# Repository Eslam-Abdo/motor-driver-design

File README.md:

# Motor Driver Design
This repository contains the latest version of my motor driver design project. My role in the project included reverse engineering a Cytron 10-A motor driver, redesigning the driver circuit using Eagle PCB tool, and designing multiple versions to improve the design.

## Latest Version
Below is a picture of the latest version of the motor driver circuit board:

|  |  |  |
| ------- | ------- | ------- |
|  |  |  |
|  |  |  |
|  |  | | |

## Files
The repository contains the following files:
- Schematics and PCB layout files for different versions of the motor driver circuit
- Pictures of the fabricated PCBs for each version

## Contact
If you are interested in my services for your next PCB design and fabrication project, please feel free to contact me.

Email: **eng-islam-abdo1722@alexu.edu.eg**

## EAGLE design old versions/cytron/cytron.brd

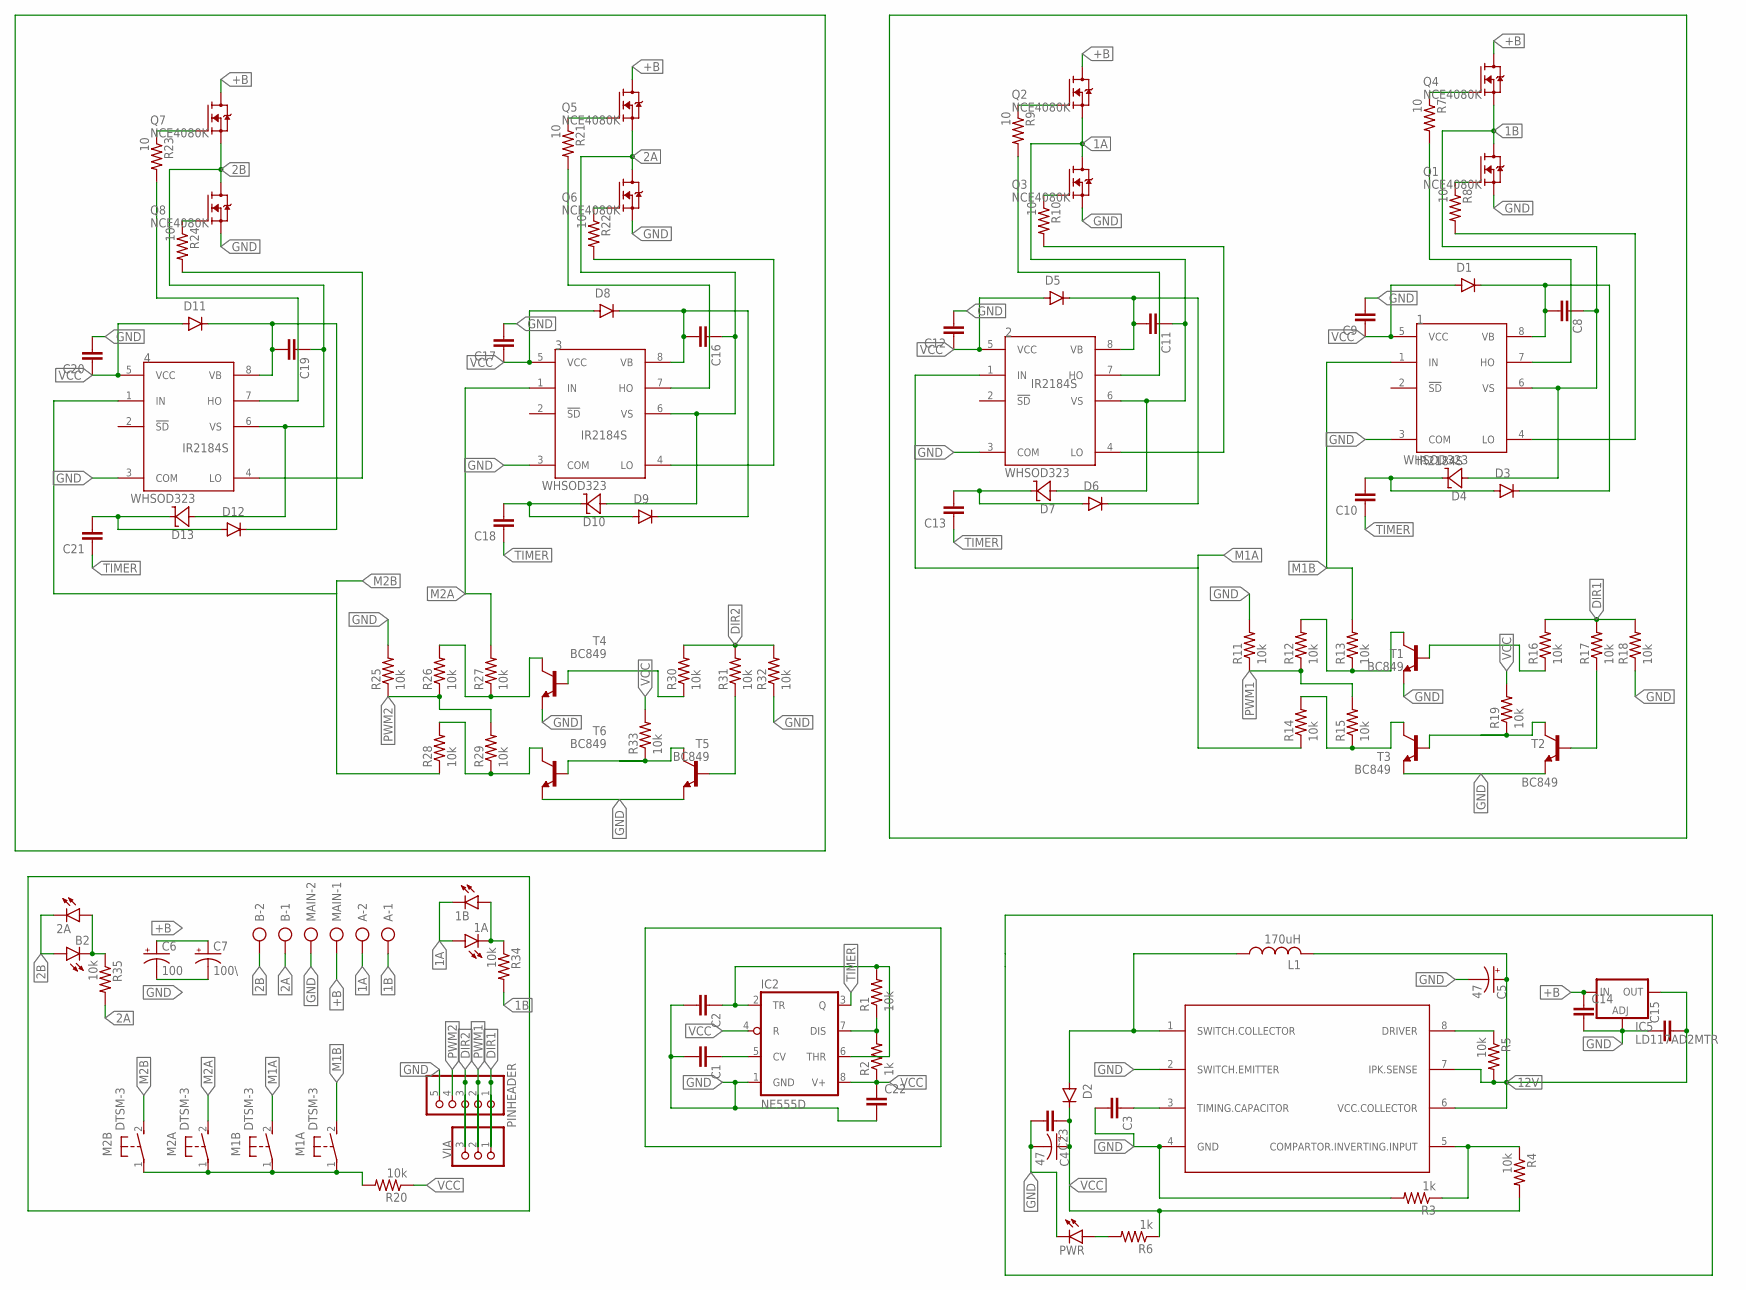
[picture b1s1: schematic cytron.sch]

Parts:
1, 2, 3, 4: IR2184S; SO08
1A, 1B, 2A: LEDCHIPLED_1206; CHIPLED_1206
A: AK300/22; XTALRR488W60L1090T465H350B
B: AK300/22; XTALRR488W60L1090T465H350B
B2: LEDCHIPLED_1206; CHIPLED_1206
C1, C2, C3, C8, C9, C10, C11, C12, C13, C14, C15, C16, C17, C18, C19, C20, C21, C22, C23: C-EUC0805K; C0805K
C4, C5: 47; 140CLH-1014
C6: 100; SANYO-OSCON_SMD_F12
C7: 100\; SANYO-OSCON_SMD_F12
D1, D2, D3, D5, D6, D8, D9, D11, D12: DIODE-SMB; SMB
D4, D7, D10, D13: WHSOD323; SOD323-W
IC2: NE555D; SO08
IC5: LD117AD2MTR; D2PACK
L1: 170uH; POWER-CHOKE_WE-TPC
M1A, M1B, M2A, M2B: DTSM-3
MAIN: AK300/22; XTALRR488W60L1090T465H350B
PINHEADER: PINHD-1X5; 1X05
PWR: LEDCHIPLED_1206; CHIPLED_1206
Q1, Q2, Q3, Q4, Q5, Q6, Q7, Q8: NCE4080K; TO252
R1, R4, R5, R11, R12, R13, R14, R15, R16, R17, R18, R19, R20, R25, R26, R27, R28, R29, R30, R31, R32, R33, R34, R35: 10k; R1206
R2, R3, R6: 1k; R1206
R7, R8, R9, R10, R21, R22, R23, R24: 10; R1206
T1, T2, T3, T4, T5, T6: BC849; SOT23
U$1: AB34063; SO8
VIA: PINHD-1X3; 1X03

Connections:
1A: 1A.A, 1B.C, 2.6 (VS), A.2, C11.1, D7.A, Q2.2 (S), Q3.3 (D)
1B: 1.6 (VS), A.1, C8.1, D4.A, Q1.3 (D), Q4.2 (S), R34.2
2A: 3.6 (VS), B.1, C16.1, D10.A, Q5.2 (S), Q6.3 (D), R35.2
2B: 2A.C, 4.6 (VS), B.2, B2.A, C19.1, D13.A, Q7.2 (S), Q8.3 (D)
12V: C5.+, C15.2, IC5.3 (OUT), L1.2, R5.2, U$1.6 (VCC.COLLECTOR), U$1.7 (IPK.SENSE)
+B: C6.+, C7.+, C14.1, IC5.1 (IN), MAIN.1, Q2.3 (D), Q4.3 (D), Q5.3 (D), Q7.3 (D)
DIR1: PINHEADER.1, R16.2, R17.2, R18.2, VIA.1
DIR2: PINHEADER.3, R30.2, R31.2, R32.2, VIA.3
GND: 1.3 (COM), 2.3 (COM), 3.3 (COM), 4.3 (COM), C1.2, C2.2, C3.2, C4.-, C5.-, C6.-, C7.-, C9.2, C12.2, C14.2, C15.1, C17.2, C20.2, C22.2, C23.2, IC2.1 (GND), IC5.2 (ADJ), MAIN.2, PINHEADER.5, PWR.C, Q1.2 (S), Q3.2 (S), Q6.2 (S), Q8.2 (S), R3.2, R11.2, R18.1, R25.2, R32.1, T1.2 (E), T2.2 (E), T3.2 (E), T4.2 (E), T5.2 (E), T6.2 (E), U$1.2 (SWITCH.EMITTER), U$1.4 (GND)
M1A: 2.1 (IN), M1B.2, R14.1
M1B: 1.1 (IN), M1A.2, R13.2
M2A: 3.1 (IN), M2A.2, R27.2
M2B: 4.1 (IN), M2B.2, R28.1
unnamed: PWR.A, R6.2
unnamed: C1.1, IC2.5 (CV)
unnamed: IC2.7 (DIS), R1.1, R2.2
unnamed: C2.1, IC2.2 (TR), IC2.6 (THR), R1.2
unnamed: C3.1, U$1.3 (TIMING.CAPACITOR)
unnamed: Q6.1 (G), R22.1
unnamed: D2.A, L1.1, U$1.1 (SWITCH.COLLECTOR)
unnamed: R5.1, U$1.8 (DRIVER)
unnamed: Q4.1 (G), R7.1
unnamed: Q1.1 (G), R8.1
unnamed: R3.1, R4.1, U$1.5 (COMPARTOR.INVERTING.INPUT)
unnamed: 1.4 (LO), R8.2
unnamed: 1.7 (HO), R7.2
unnamed: C10.2, D3.A, D4.C
unnamed: Q3.1 (G), R10.1
unnamed: Q2.1 (G), R9.1
unnamed: 2.4 (LO), R10.2
unnamed: 2.7 (HO), R9.2
unnamed: R16.1, T1.1 (B)
unnamed: C13.2, D6.A, D7.C
unnamed: M1A.1, M1B.1, M2A.1, M2B.1, R20.2
unnamed: R14.2, R15.1, T3.3 (C)
unnamed: R12.2, R13.1, T1.3 (C)
unnamed: Q5.1 (G), R21.1
unnamed: 3.4 (LO), R22.2
unnamed: R19.1, T2.3 (C), T3.1 (B)
unnamed: R17.1, T2.1 (B)
unnamed: 3.7 (HO), R21.2
unnamed: C18.2, D9.A, D10.C
unnamed: Q8.1 (G), R24.1
unnamed: Q7.1 (G), R23.1
unnamed: 4.4 (LO), R24.2
unnamed: 4.7 (HO), R23.2
unnamed: C21.2, D12.A, D13.C
unnamed: R28.2, R29.1, T6.3 (C)
unnamed: R26.2, R27.1, T4.3 (C)
unnamed: R30.1, T4.1 (B)
unnamed: R33.1, T5.3 (C), T6.1 (B)
unnamed: R31.1, T5.1 (B)
unnamed: 1A.C, 1B.A, R34.1
unnamed: 2A.A, B2.C, R35.1
PWM1: PINHEADER.2, R11.1, R12.1, R15.2, VIA.2
PWM2: PINHEADER.4, R25.1, R26.1, R29.2
TIMER: C10.1, C13.1, C18.1, C21.1, IC2.3 (Q)
VB1: 1.8 (VB), C8.2, D1.C, D3.C
VB2: 2.8 (VB), C11.2, D5.C, D6.C
VB3: 3.8 (VB), C16.2, D8.C, D9.C
VB4: 4.8 (VB), C19.2, D11.C, D12.C
VCC: 1.5 (VCC), 2.5 (VCC), 3.5 (VCC), 4.5 (VCC), C4.+, C9.1, C12.1, C17.1, C20.1, C22.1, C23.1, D1.A, D2.C, D5.A, D8.A, D11.A, IC2.4 (R), IC2.8 (V+), R2.1, R4.2, R6.1, R19.2, R20.1, R33.2

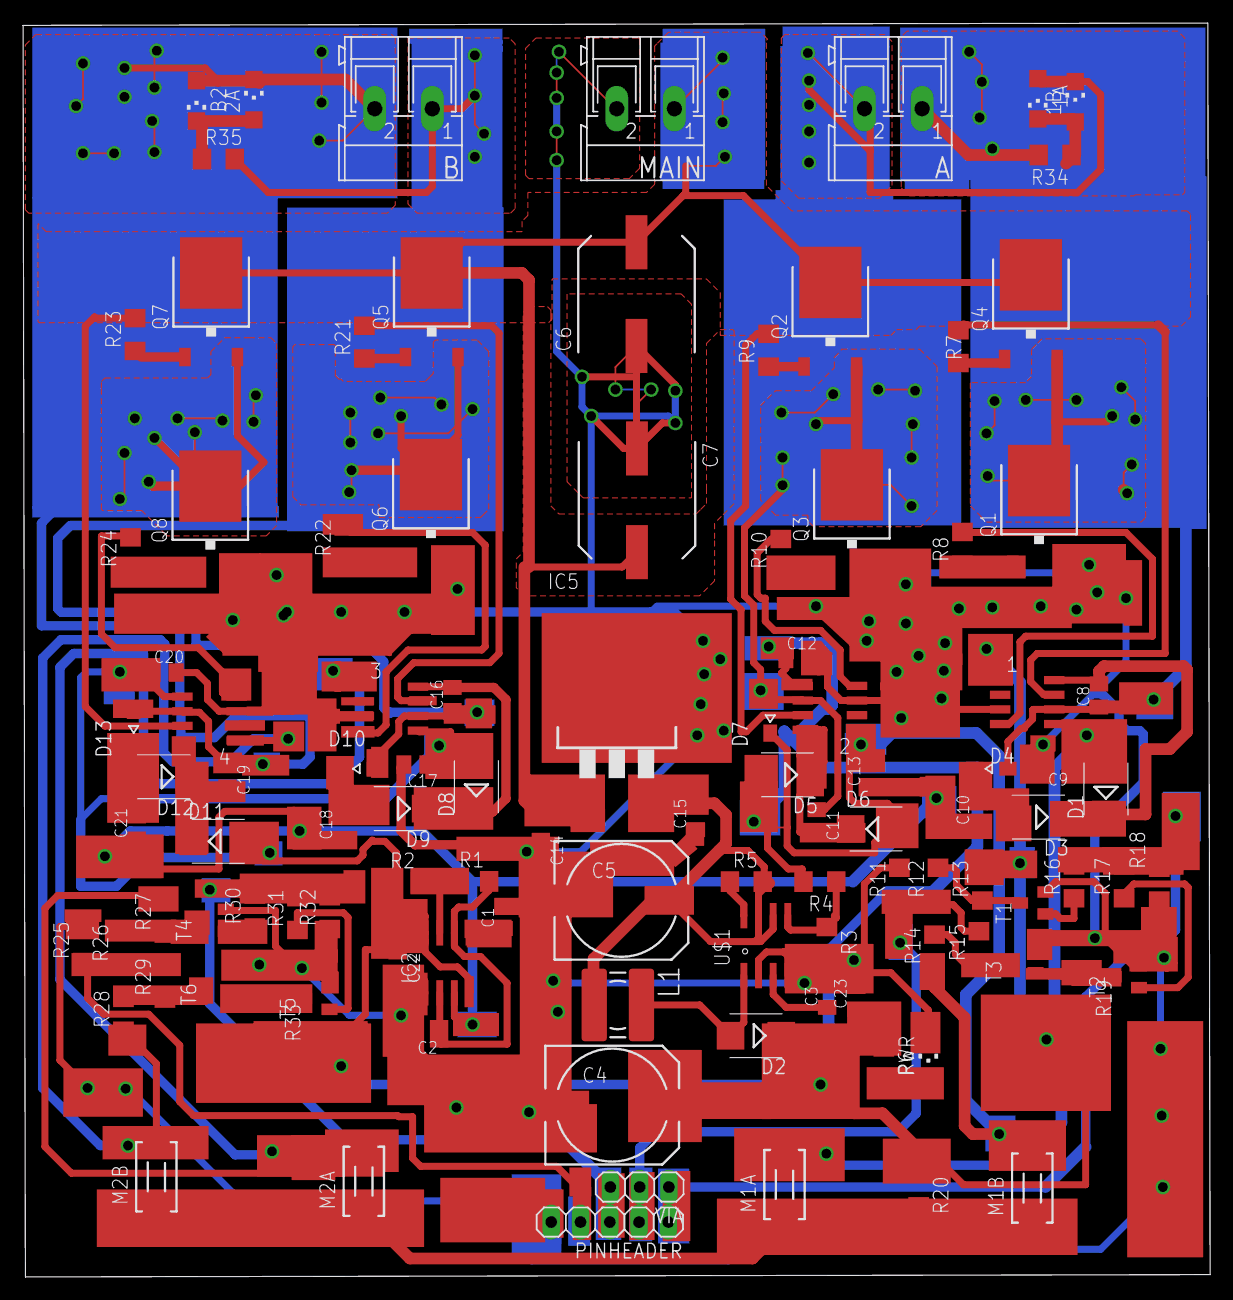
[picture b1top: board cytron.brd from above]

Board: 2 copper layers, 103.0 x 108.8 mm, 107 parts (0 on the bottom side), 62 nets.

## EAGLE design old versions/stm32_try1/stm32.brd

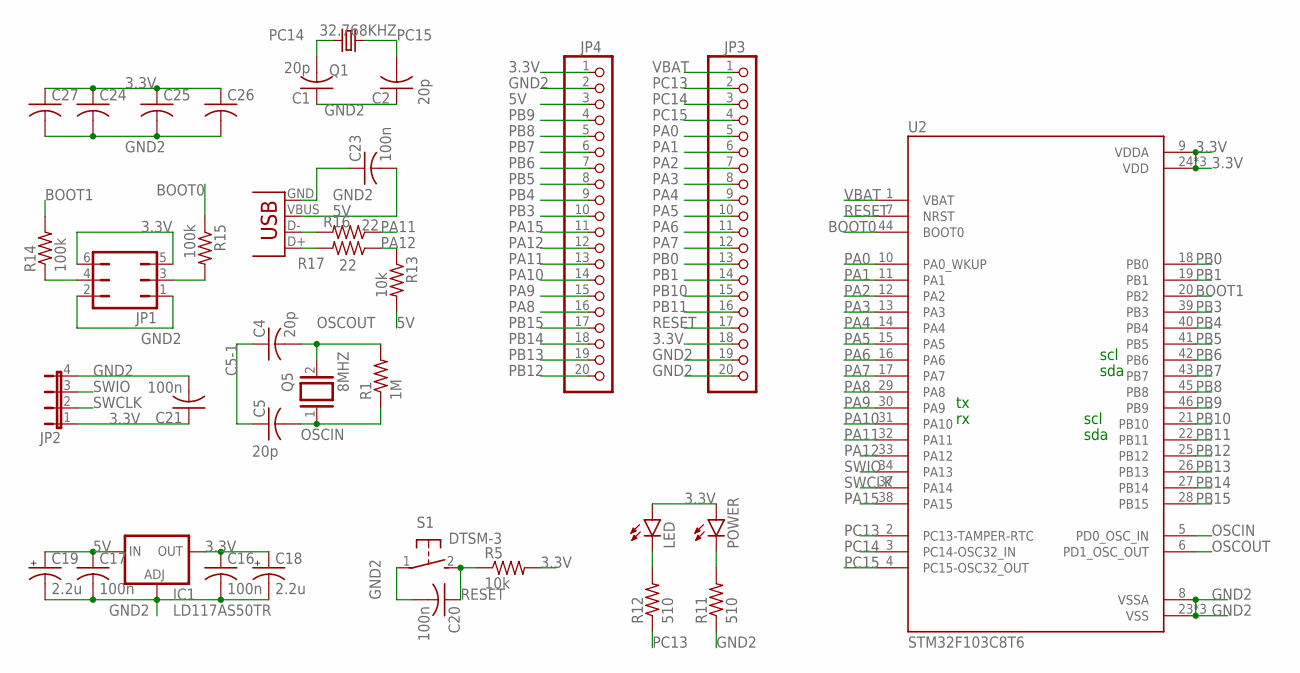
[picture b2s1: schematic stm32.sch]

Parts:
C1, C2, C4, C5: 20p; C1206
C16, C17, C20, C21, C23: 100n; C1206
C18, C19: 2.2u; E2-5
C24, C25, C26, C27: C-USC1206; C1206
IC1: LD117AS50TR; SOT223
JP1: JP3Q
JP2: JP4E; JP4
JP3, JP4: PINHD-1X20; 1X20
LED: LEDCHIPLED_1206; CHIPLED_1206
POWER: LEDCHIPLED_1206; CHIPLED_1206
Q1: 32.768KHZ; TC26H
Q5: 8MHZ; QS
R1: 1M; R1206
R5, R13: 10k; R1206
R11, R12: 510; R1206
R14, R15: 100k; R1206
R16, R17: 22; R1206
S1: DTSM-3
U2: STM32F103C8T6; QFP50P900X900X160-48N
X1: USB-MB-S

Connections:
3.3V: C16.1, C18.+, C21.1, C24.1, C25.1, C26.1, C27.1, IC1.4 (OUT), JP1.5, JP1.6, JP2.1, JP3.18, JP4.1, LED.A, POWER.A, R5.2, U2.9 (VDDA), U2.24 (VDD), U2.36 (VDD), U2.48 (VDD)
5V: C17.1, C19.+, C23.2, IC1.3 (IN), JP4.3, R13.2, X1.VBUS
BOOT0: R15.1, U2.44 (BOOT0)
BOOT1: R14.2, U2.20 (PB2)
C5-1: C4.1, C5.1
GND2: C1.1, C2.1, C16.2, C17.2, C18.-, C19.-, C20.2, C21.2, C23.1, C24.2, C25.2, C26.2, C27.2, IC1.1 (ADJ), JP1.1, JP1.2, JP2.4, JP3.19, JP3.20, JP4.2, R11.1, S1.1, U2.8 (VSSA), U2.23 (VSS), U2.35 (VSS), U2.47 (VSS), X1.GND
unnamed: LED.C, R12.2
unnamed: POWER.C, R11.2
unnamed: JP1.3, R15.2
unnamed: JP1.4, R14.1
unnamed: R16.2, X1.D-
unnamed: R17.2, X1.D+
OSCIN: C5.2, Q5.1, R1.1, U2.5 (PD0_OSC_IN)
OSCOUT: C4.2, Q5.2, R1.2, U2.6 (PD1_OSC_OUT)
PA0: JP3.5, U2.10 (PA0_WKUP)
PA1: JP3.6, U2.11 (PA1)
PA2: JP3.7, U2.12 (PA2)
PA3: JP3.8, U2.13 (PA3)
PA4: JP3.9, U2.14 (PA4)
PA5: JP3.10, U2.15 (PA5)
PA6: JP3.11, U2.16 (PA6)
PA7: JP3.12, U2.17 (PA7)
PA8: JP4.16, U2.29 (PA8)
PA9: JP4.15, U2.30 (PA9)
PA10: JP4.14, U2.31 (PA10)
PA11: JP4.13, R16.1, U2.32 (PA11)
PA12: JP4.12, R13.1, R17.1, U2.33 (PA12)
PA15: JP4.11, U2.38 (PA15)
PB0: JP3.13, U2.18 (PB0)
PB1: JP3.14, U2.19 (PB1)
PB3: JP4.10, U2.39 (PB3)
PB4: JP4.9, U2.40 (PB4)
PB5: JP4.8, U2.41 (PB5)
PB6: JP4.7, U2.42 (PB6)
PB7: JP4.6, U2.43 (PB7)
PB8: JP4.5, U2.45 (PB8)
PB9: JP4.4, U2.46 (PB9)
PB10: JP3.15, U2.21 (PB10)
PB11: JP3.16, U2.22 (PB11)
PB12: JP4.20, U2.25 (PB12)
PB13: JP4.19, U2.26 (PB13)
PB14: JP4.18, U2.27 (PB14)
PB15: JP4.17, U2.28 (PB15)
PC13: JP3.2, R12.1, U2.2 (PC13-TAMPER-RTC)
PC14: C1.2, JP3.3, Q1.2, U2.3 (PC14-OSC32_IN)
PC15: C2.2, JP3.4, Q1.1, U2.4 (PC15-OSC32_OUT)
RESET: C20.1, JP3.17, R5.1, S1.2, U2.7 (NRST)
SWCLK: JP2.2, U2.37 (PA14)
SWIO: JP2.3, U2.34 (PA13)
VBAT: JP3.1, U2.1 (VBAT)

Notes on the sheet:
scl
sda

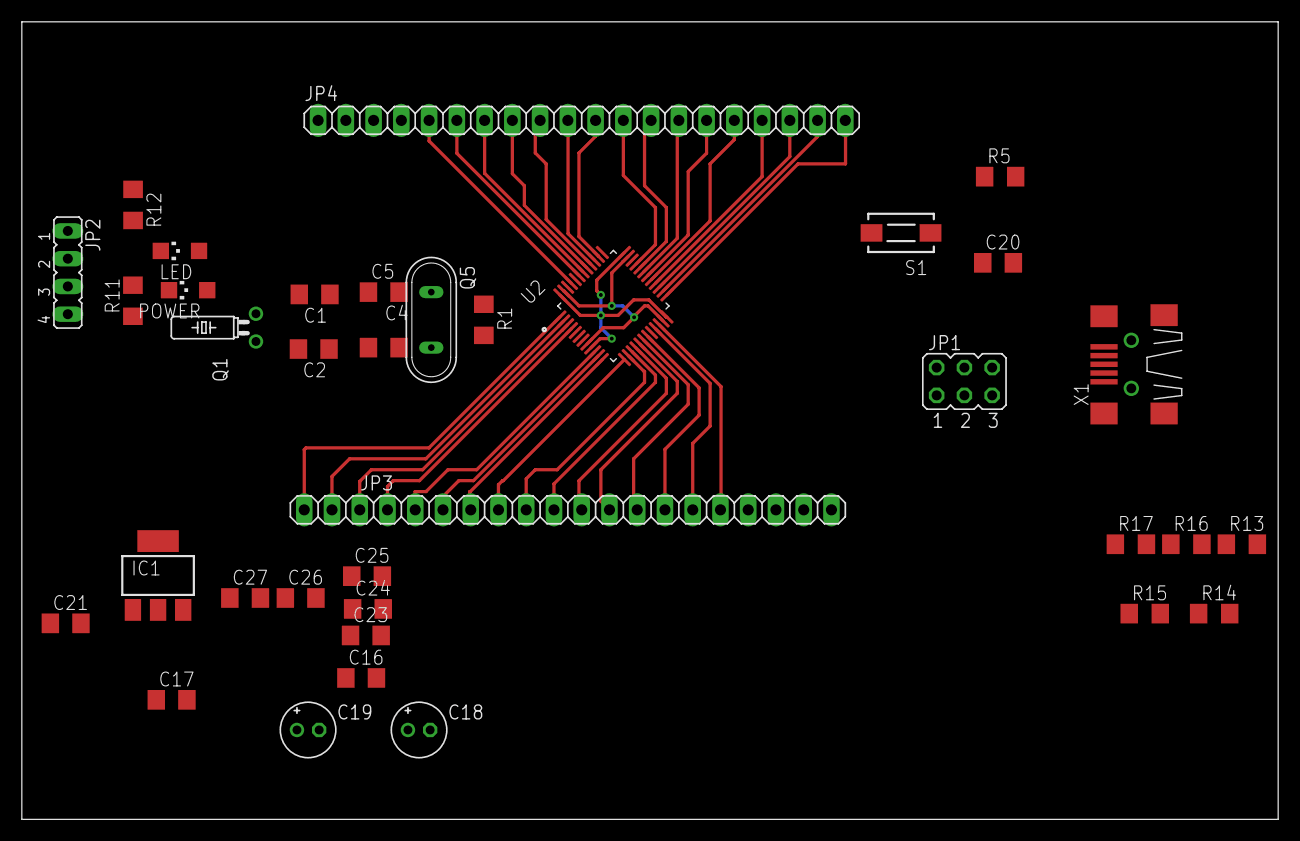
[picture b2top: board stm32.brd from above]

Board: 2 copper layers, 115.0 x 73.0 mm, 36 parts (0 on the bottom side), 50 nets.

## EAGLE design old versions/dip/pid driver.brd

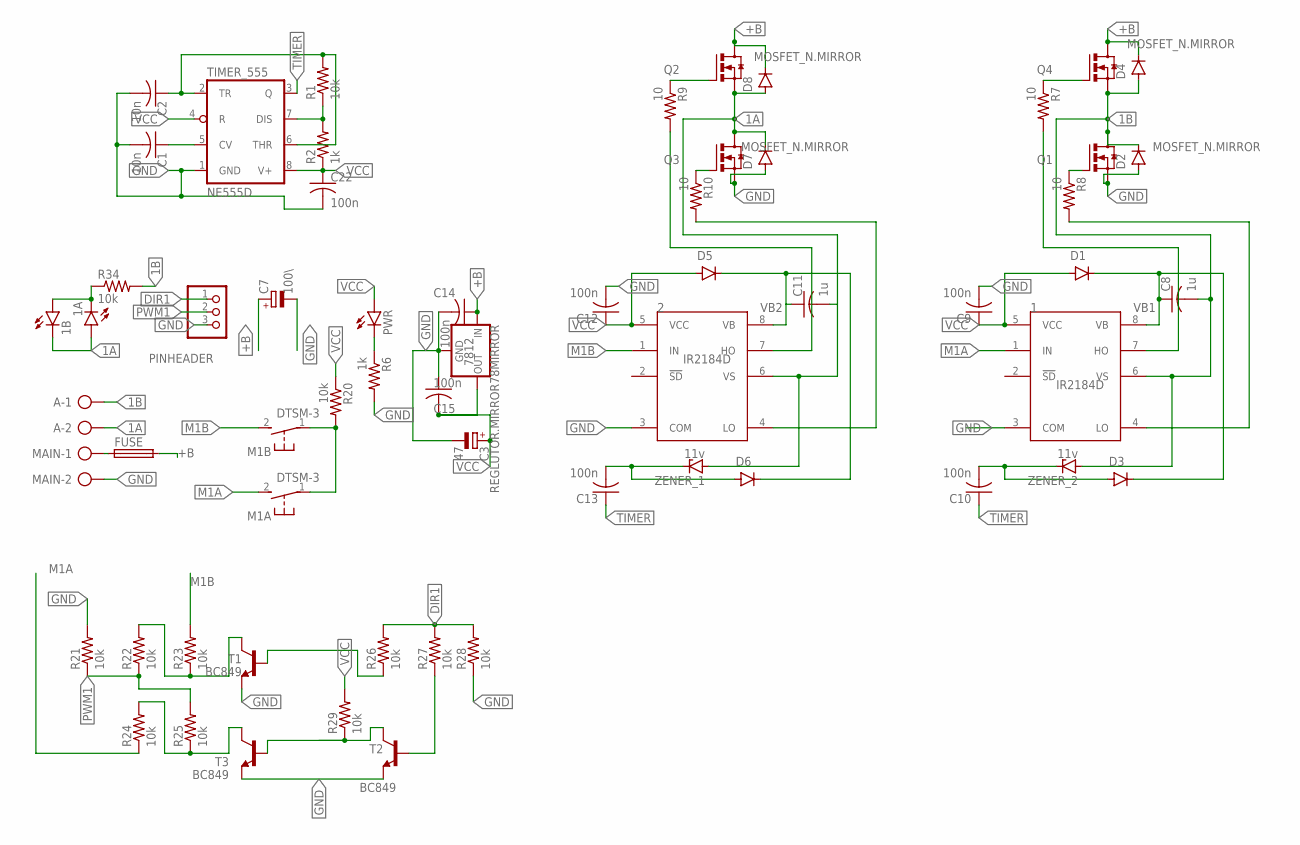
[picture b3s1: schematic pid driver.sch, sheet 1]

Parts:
1, 2: IR2184D; DIL08
1A, 1B: LEDCHIPLED_1206; CHIPLED_1206
7812: REGLUTOR.MIRROR78MIRROR; 78MIRROR
A: AK300/22; XTALRR488W60L1090T465H350B
C1, C2: 10n; C1206K
C3: 47; E5-10,5
C7: 100\; E5-10,5
C8, C11: 1u; C1206K
C9, C10, C12, C13, C14, C15, C22: 100n; C1206K
D1, D2, D3, D4, D5, D6, D7, D8: DIODE-SMB; SMB
FUSE: FUSE_HOLDER; SH22,5A
M1A, M1B: DTSM-3
MAIN: AK300/22; XTALRR488W60L1090T465H350B
PINHEADER: PINHD-1X3; 1X03
PWR: LEDCHIPLED_1206; CHIPLED_1206
Q1, Q2, Q3, Q4: MOSFET_N.MIRROR; TO220.MIRROR
R1, R20, R34: 10k; M1206
R2, R6: 1k; M1206
R7, R8, R9, R10: 10; M1206
R21, R22, R23, R24, R25, R26, R27, R28, R29: 10k; R1206
T1, T2, T3: BC849; SOT23
TIMER_555: NE555D; SO08
ZENER_1, ZENER_2: 11v; SOD80C

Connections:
1A: 1A.A, 1B.C, 2.6 (VS), A.2, C11.2, D7.C, D8.A, Q2.S, Q3.D, ZENER_1.A
1B: 1.6 (VS), A.1, C8.2, D2.C, D4.A, Q1.D, Q4.S, R34.2, ZENER_2.A
+B: 7812.IN, C7.+, C14.1, D4.C, D8.C, FUSE.2, Q2.D, Q4.D
DIR1: PINHEADER.1, R26.2, R27.2, R28.2
GND: 1.3 (COM), 2.3 (COM), 7812.GND, C1.2, C2.2, C3.-, C7.-, C9.2, C12.2, C14.2, C15.1, C22.2, D2.A, D7.A, MAIN.2, PINHEADER.3, Q1.S, Q3.S, R6.2, R21.2, R28.1, T1.2 (E), T2.2 (E), T3.2 (E), TIMER_555.1 (GND)
M1A: 1.1 (IN), M1A.2, R24.1
M1B: 2.1 (IN), M1B.2, R23.2
unnamed: PWR.C, R6.1
unnamed: C1.1, TIMER_555.5 (CV)
unnamed: R1.1, R2.2, TIMER_555.7 (DIS)
unnamed: C2.1, R1.2, TIMER_555.2 (TR), TIMER_555.6 (THR)
unnamed: M1A.1, M1B.1, R20.2
unnamed: Q4.G, R7.1
unnamed: Q1.G, R8.1
unnamed: 1.4 (LO), R8.2
unnamed: 1.7 (HO), R7.2
unnamed: C10.2, D3.A, ZENER_2.C
unnamed: Q3.G, R10.1
unnamed: Q2.G, R9.1
unnamed: 2.4 (LO), R10.2
unnamed: 2.7 (HO), R9.2
unnamed: C13.2, D6.A, ZENER_1.C
unnamed: FUSE.1, MAIN.1
unnamed: R24.2, R25.1, T3.3 (C)
unnamed: R22.2, R23.1, T1.3 (C)
unnamed: R26.1, T1.1 (B)
unnamed: R29.1, T2.3 (C), T3.1 (B)
unnamed: R27.1, T2.1 (B)
unnamed: 1A.C, 1B.A, R34.1
PWM1: PINHEADER.2, R21.1, R22.1, R25.2
TIMER: C10.1, C13.1, TIMER_555.3 (Q)
VB1: 1.8 (VB), C8.1, D1.C, D3.C
VB2: 2.8 (VB), C11.1, D5.C, D6.C
VCC: 1.5 (VCC), 2.5 (VCC), 7812.OUT, C3.+, C9.1, C12.1, C15.2, C22.1, D1.A, D5.A, PWR.A, R2.1, R20.1, R29.2, TIMER_555.4 (R), TIMER_555.8 (V+)

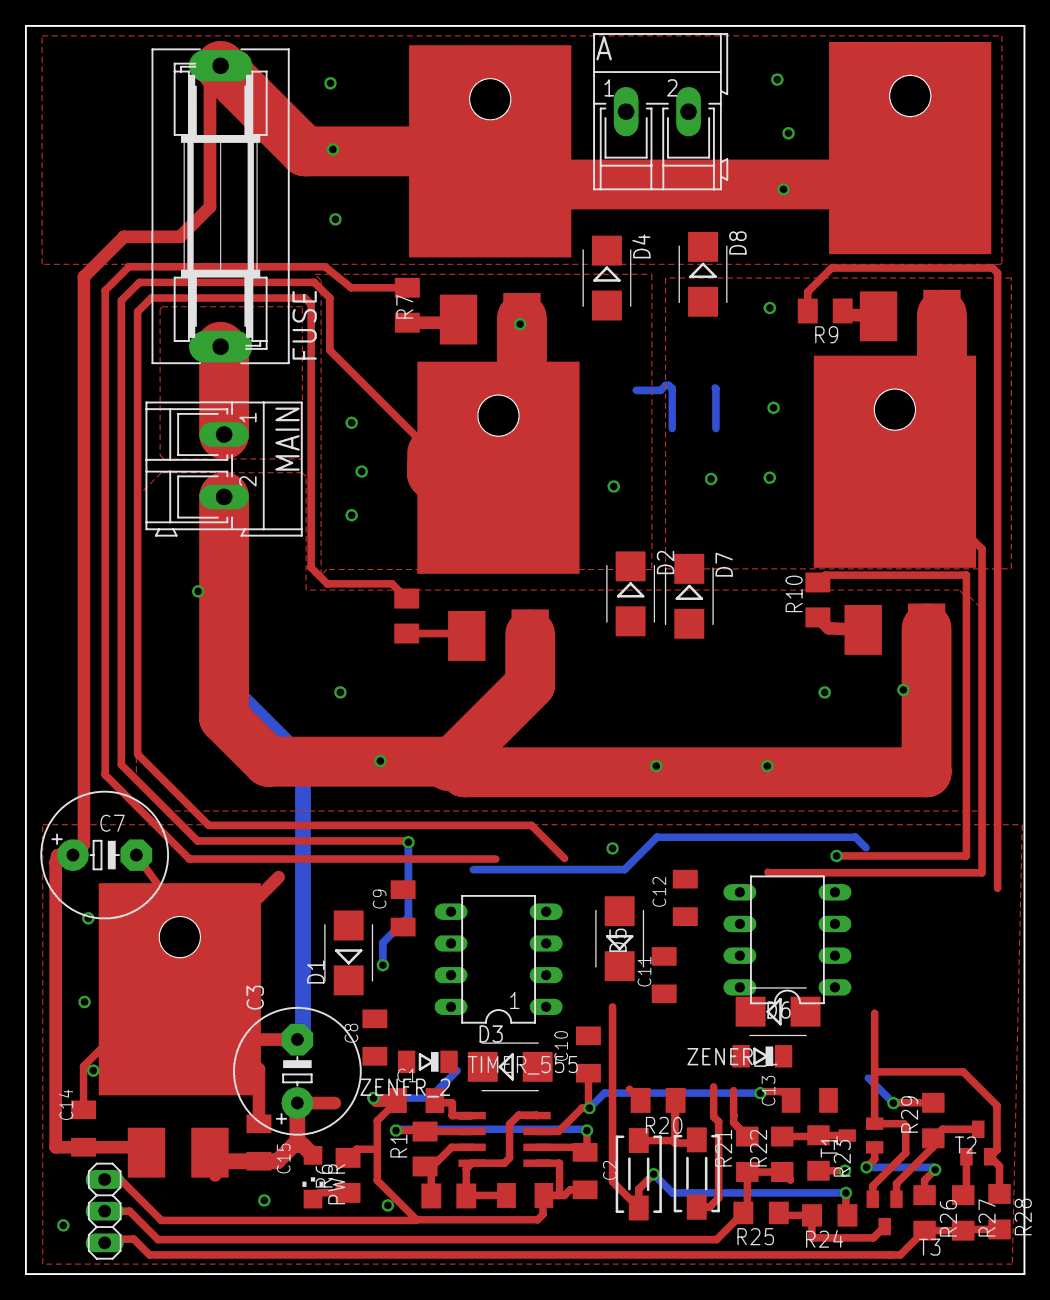
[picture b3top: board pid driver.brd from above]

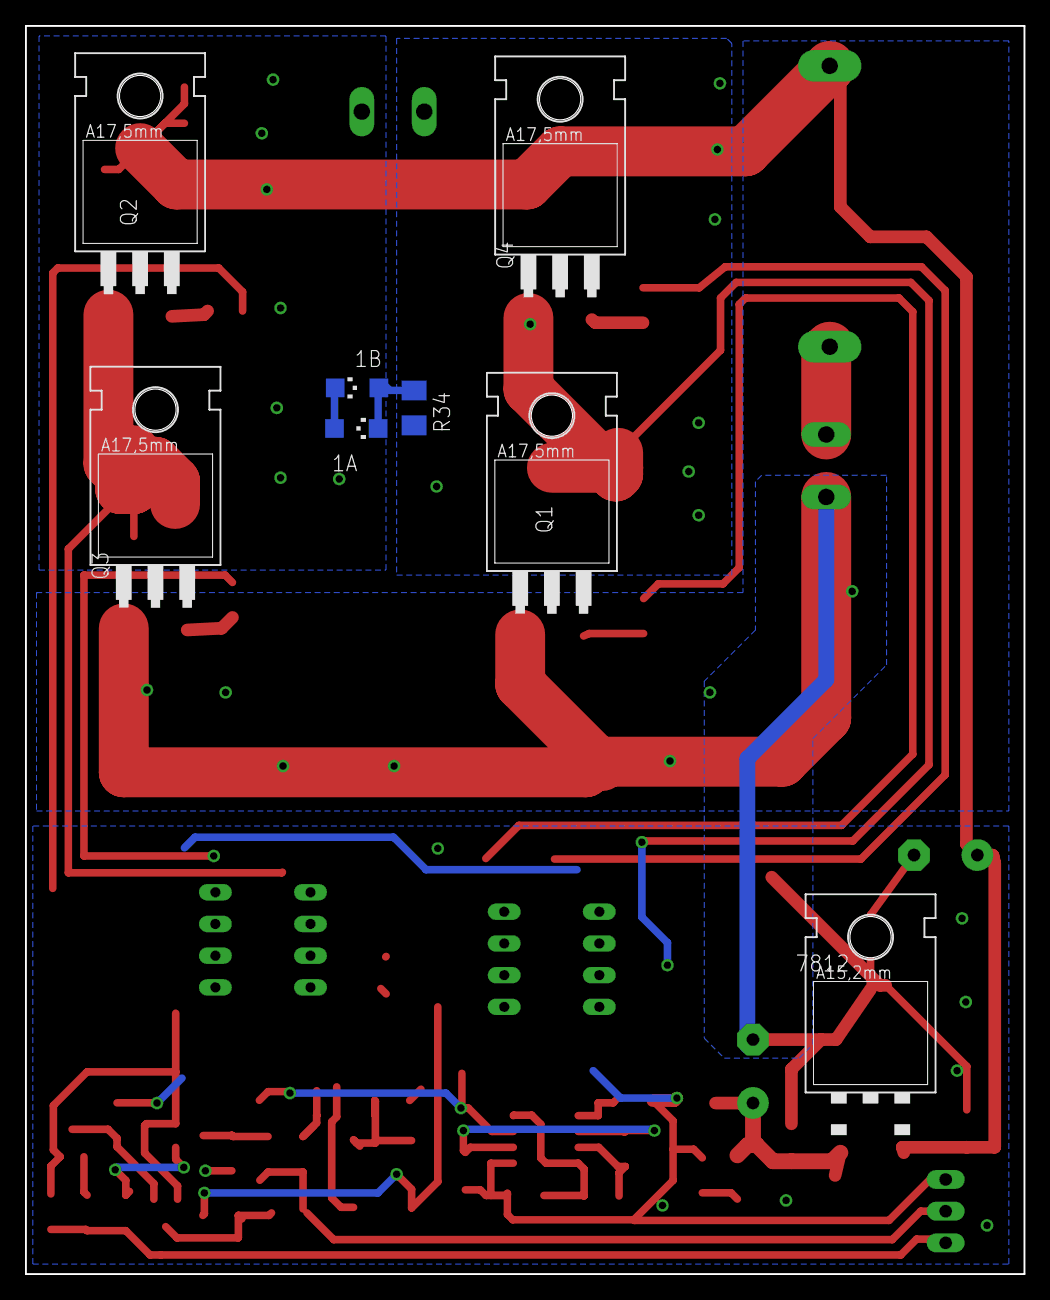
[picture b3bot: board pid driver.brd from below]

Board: 2 copper layers, 80.0 x 100.0 mm, 61 parts (8 on the bottom side), 34 nets.

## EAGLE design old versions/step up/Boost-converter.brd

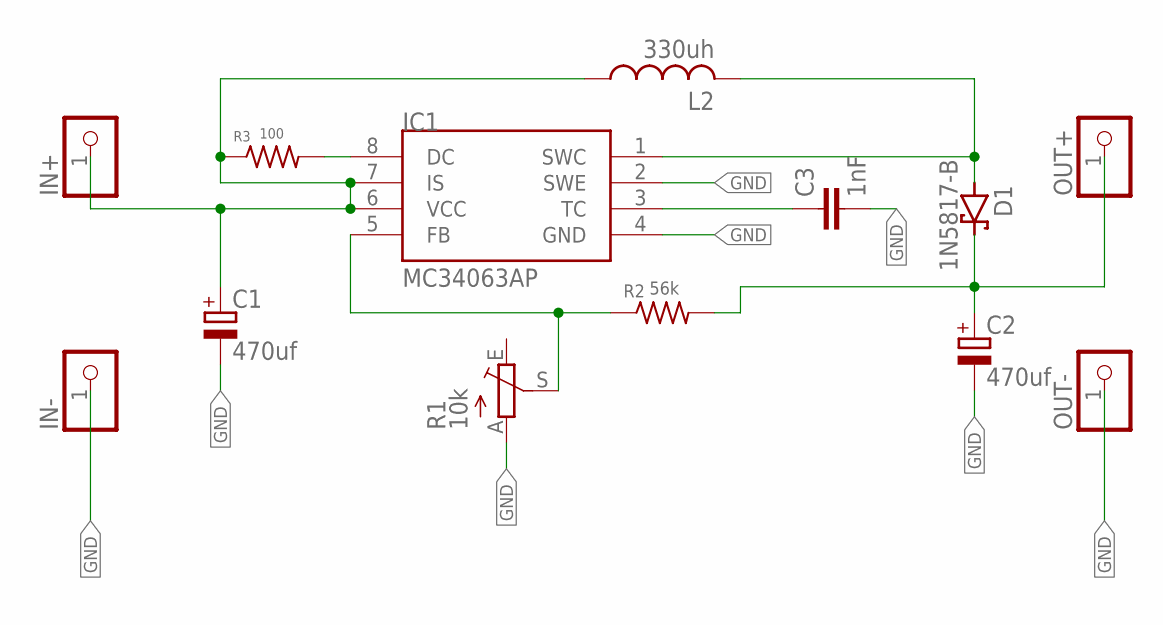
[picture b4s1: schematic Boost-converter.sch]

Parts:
C1, C2: 470uf; E3,5-8
C3: 1nF; C025-025X050
D1: 1N5817-B; DO41-7.6
IC1: MC34063AP; DIL08
IN+: PINHD-1X1; 1X01
IN-: PINHD-1X1; 1X01
L2: 330uh; 0207/10
OUT+: PINHD-1X1; 1X01
OUT-: PINHD-1X1; 1X01
R1: 10k; CA6V
R2: 56k; 0204/7
R3: 100; 0204/7

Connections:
GND: C1.-, C2.-, C3.2, IC1.2 (SWE), IC1.4 (GND), IN-.1, OUT-.1, R1.A
IN: C2.+, D1.C, OUT+.1, R2.2
unnamed: C1.+, IC1.6 (VCC), IC1.7 (IS), IN+.1, L2.1, R3.1
unnamed: D1.A, IC1.1 (SWC), L2.2
unnamed: IC1.5 (FB), R1.S, R2.1
unnamed: C3.1, IC1.3 (TC)
unnamed: IC1.8 (DC), R3.2

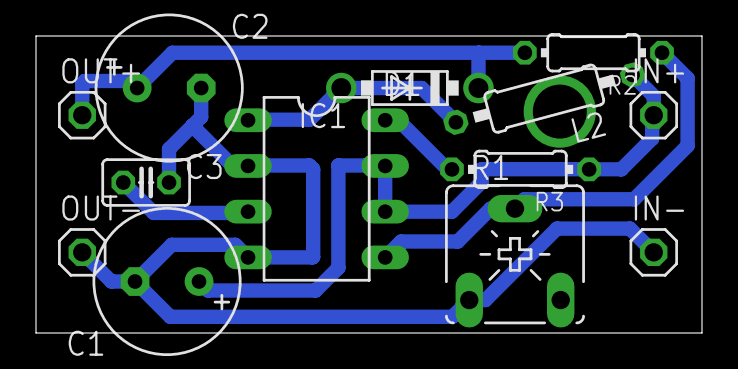
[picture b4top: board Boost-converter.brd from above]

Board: 2 copper layers, 37.0 x 16.5 mm, 13 parts (0 on the bottom side), 7 nets.

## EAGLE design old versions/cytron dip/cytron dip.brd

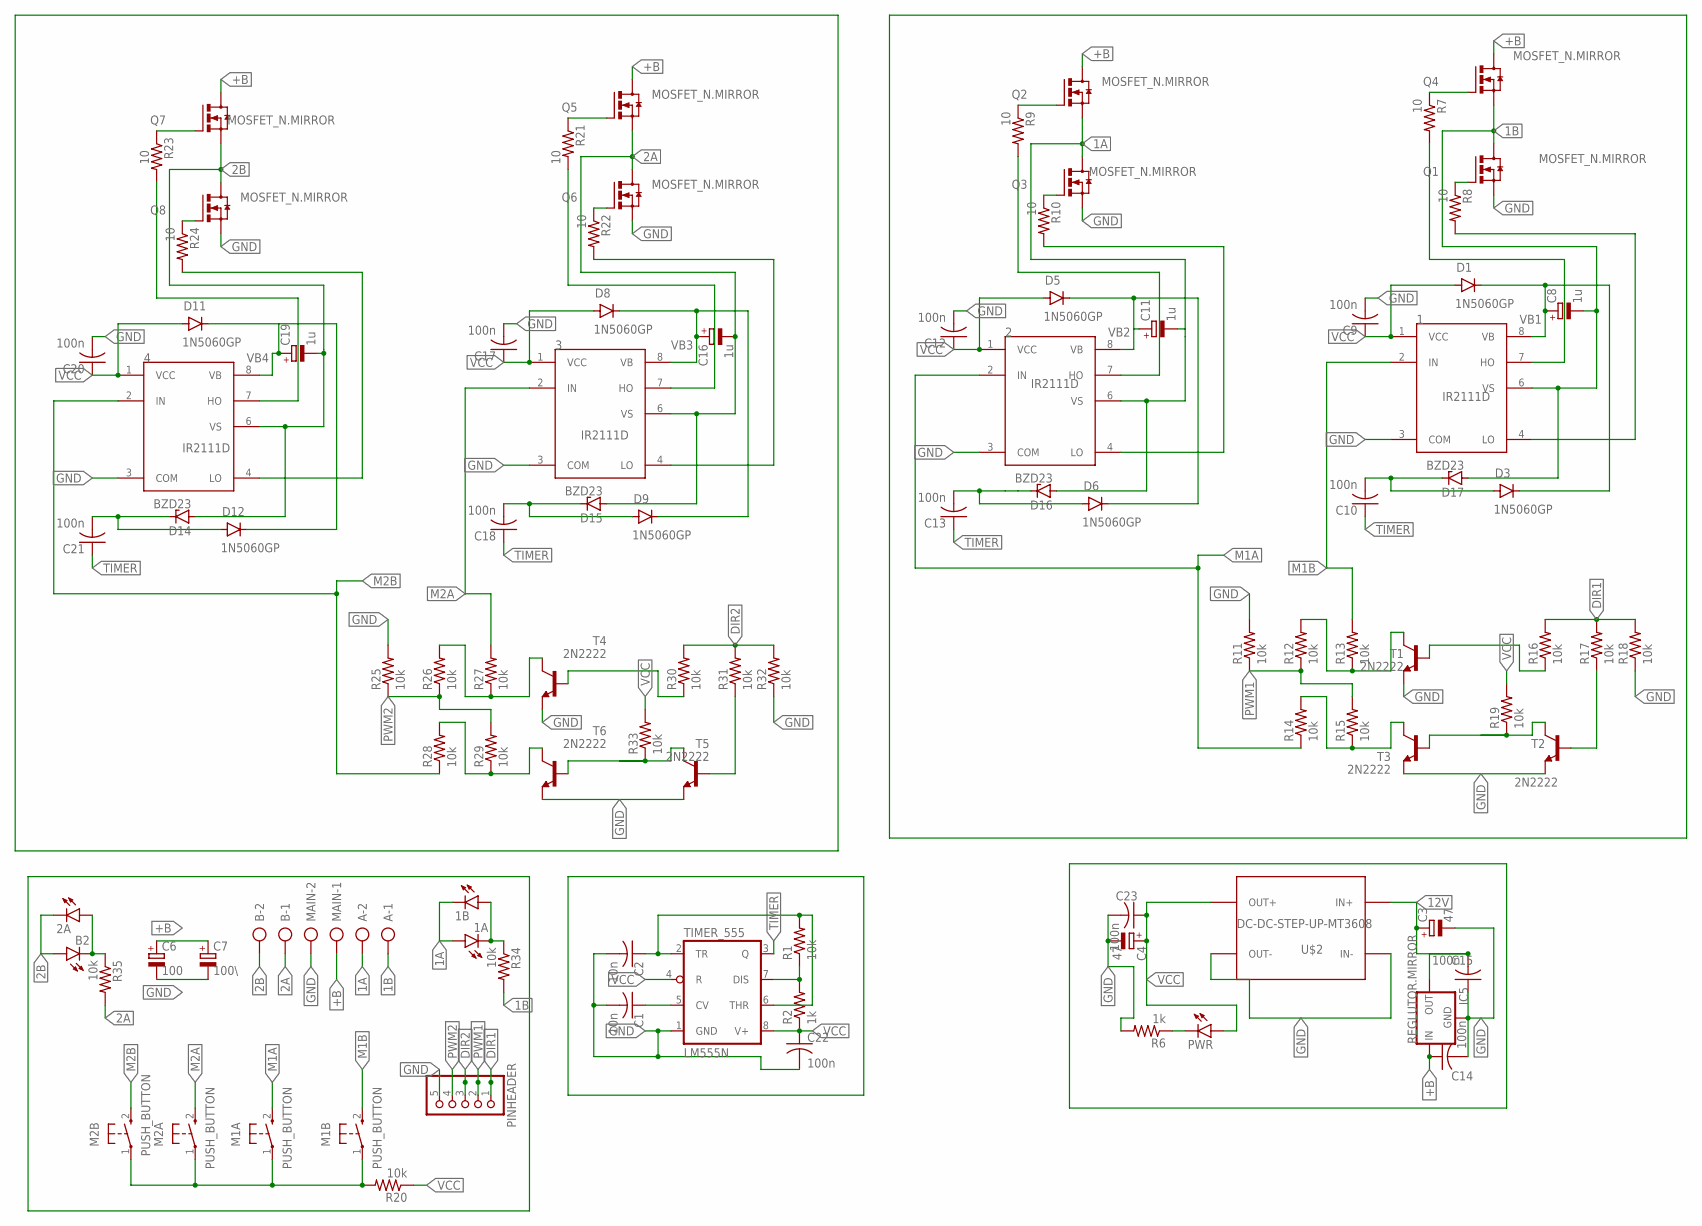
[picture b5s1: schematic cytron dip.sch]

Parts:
1, 2, 3, 4: IR2111D; DIL08
1A, 1B, 2A: LED3MM
A: AK300/22; XTALRR488W60L1090T465H350B
B: AK300/22; XTALRR488W60L1090T465H350B
B2: LED3MM
C1, C2: 10n; C025-025X050
C3, C4: 47; E5-10,5
C6: 100; E5-10,5
C7: 100\; E5-10,5
C8, C11, C16, C19: 1u; E5-5
C9, C10, C12, C13, C14, C15, C17, C18, C20, C21, C22, C23: 100n; C025-025X050
D1, D3, D5, D6, D8, D9, D11, D12: 1N5060GP; DO15-12
D14, D15, D16, D17: BZD23; SOD81
IC5: REGLUTOR.MIRROR; 78XXL.MIRROR
M1A, M1B, M2A, M2B: PUSH_BUTTON; B3F-10XX
MAIN: AK300/22; XTALRR488W60L1090T465H350B
PINHEADER: PINHD-1X5; 1X05
PWR: LED5MM
Q1, Q2, Q3, Q4, Q5, Q6, Q7, Q8: MOSFET_N.MIRROR; TO220.MIRROR
R1, R11, R12, R13, R14, R15, R16, R17, R18, R19, R20, R25, R26, R27, R28, R29, R30, R31, R32, R33, R34, R35: 10k; 0204/7
R2, R6: 1k; 0204/7
R7, R8, R9, R10, R21, R22, R23, R24: 10; 0204/7
T1, T2, T3, T4, T5, T6: 2N2222; TO18
TIMER_555: LM555N; DIL08
U$2: DC-DC-STEP-UP-MT3608

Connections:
1A: 1A.A, 1B.K (C), 2.6 (VS), A.2, C11.-, D16.A, Q2.S, Q3.D
1B: 1.6 (VS), A.1, C8.-, D17.A, Q1.D, Q4.S, R34.2
2A: 3.6 (VS), B.1, C16.-, D15.A, Q5.S, Q6.D, R35.2
2B: 2A.K (C), 4.6 (VS), B.2, B2.A, C19.-, D14.A, Q7.S, Q8.D
12V: C3.+, C15.2, IC5.OUT, U$2.IN+
+B: C6.+, C7.+, C14.1, IC5.IN, MAIN.1, Q2.D, Q4.D, Q5.D, Q7.D
DIR1: PINHEADER.1, R16.2, R17.2, R18.2
DIR2: PINHEADER.3, R30.2, R31.2, R32.2
GND: 1.3 (COM), 2.3 (COM), 3.3 (COM), 4.3 (COM), C1.2, C2.2, C3.-, C4.-, C6.-, C7.-, C9.2, C12.2, C14.2, C15.1, C17.2, C20.2, C22.2, C23.2, IC5.GND, MAIN.2, PINHEADER.5, Q1.S, Q3.S, Q6.S, Q8.S, R6.2, R11.2, R18.1, R25.2, R32.1, T1.1 (E), T2.1 (E), T3.1 (E), T4.1 (E), T5.1 (E), T6.1 (E), TIMER_555.1 (GND), U$2.IN-, U$2.OUT-
M1A: 2.2 (IN), M1A.2 (S), R14.1
M1B: 1.2 (IN), M1B.2 (S), R13.2
M2A: 3.2 (IN), M2A.2 (S), R27.2
M2B: 4.2 (IN), M2B.2 (S), R28.1
unnamed: PWR.K (C), R6.1
unnamed: C1.1, TIMER_555.5 (CV)
unnamed: R1.1, R2.2, TIMER_555.7 (DIS)
unnamed: C2.1, R1.2, TIMER_555.2 (TR), TIMER_555.6 (THR)
unnamed: Q6.G, R22.1
unnamed: M1A.1, M1B.1, M2A.1, M2B.1, R20.2
unnamed: Q4.G, R7.1
unnamed: Q1.G, R8.1
unnamed: 1.4 (LO), R8.2
unnamed: 1.7 (HO), R7.2
unnamed: C10.2, D3.A, D17.C
unnamed: Q3.G, R10.1
unnamed: Q2.G, R9.1
unnamed: 2.4 (LO), R10.2
unnamed: 2.7 (HO), R9.2
unnamed: R16.1, T1.2 (B)
unnamed: C13.2, D6.A, D16.C
unnamed: R14.2, R15.1, T3.3 (C)
unnamed: R12.2, R13.1, T1.3 (C)
unnamed: Q5.G, R21.1
unnamed: 3.4 (LO), R22.2
unnamed: R19.1, T2.3 (C), T3.2 (B)
unnamed: R17.1, T2.2 (B)
unnamed: 3.7 (HO), R21.2
unnamed: C18.2, D9.A, D15.C
unnamed: Q8.G, R24.1
unnamed: Q7.G, R23.1
unnamed: 4.4 (LO), R24.2
unnamed: 4.7 (HO), R23.2
unnamed: C21.2, D12.A, D14.C
unnamed: R28.2, R29.1, T6.3 (C)
unnamed: R26.2, R27.1, T4.3 (C)
unnamed: R30.1, T4.2 (B)
unnamed: R33.1, T5.3 (C), T6.2 (B)
unnamed: R31.1, T5.2 (B)
unnamed: 1A.K (C), 1B.A, R34.1
unnamed: 2A.A, B2.K (C), R35.1
PWM1: PINHEADER.2, R11.1, R12.1, R15.2
PWM2: PINHEADER.4, R25.1, R26.1, R29.2
TIMER: C10.1, C13.1, C18.1, C21.1, TIMER_555.3 (Q)
VB1: 1.8 (VB), C8.+, D1.C, D3.C
VB2: 2.8 (VB), C11.+, D5.C, D6.C
VB3: 3.8 (VB), C16.+, D8.C, D9.C
VB4: 4.8 (VB), C19.+, D11.C, D12.C
VCC: 1.1 (VCC), 2.1 (VCC), 3.1 (VCC), 4.1 (VCC), C4.+, C9.1, C12.1, C17.1, C20.1, C22.1, C23.1, D1.A, D5.A, D8.A, D11.A, PWR.A, R2.1, R19.2, R20.1, R33.2, TIMER_555.4 (R), TIMER_555.8 (V+), U$2.OUT+

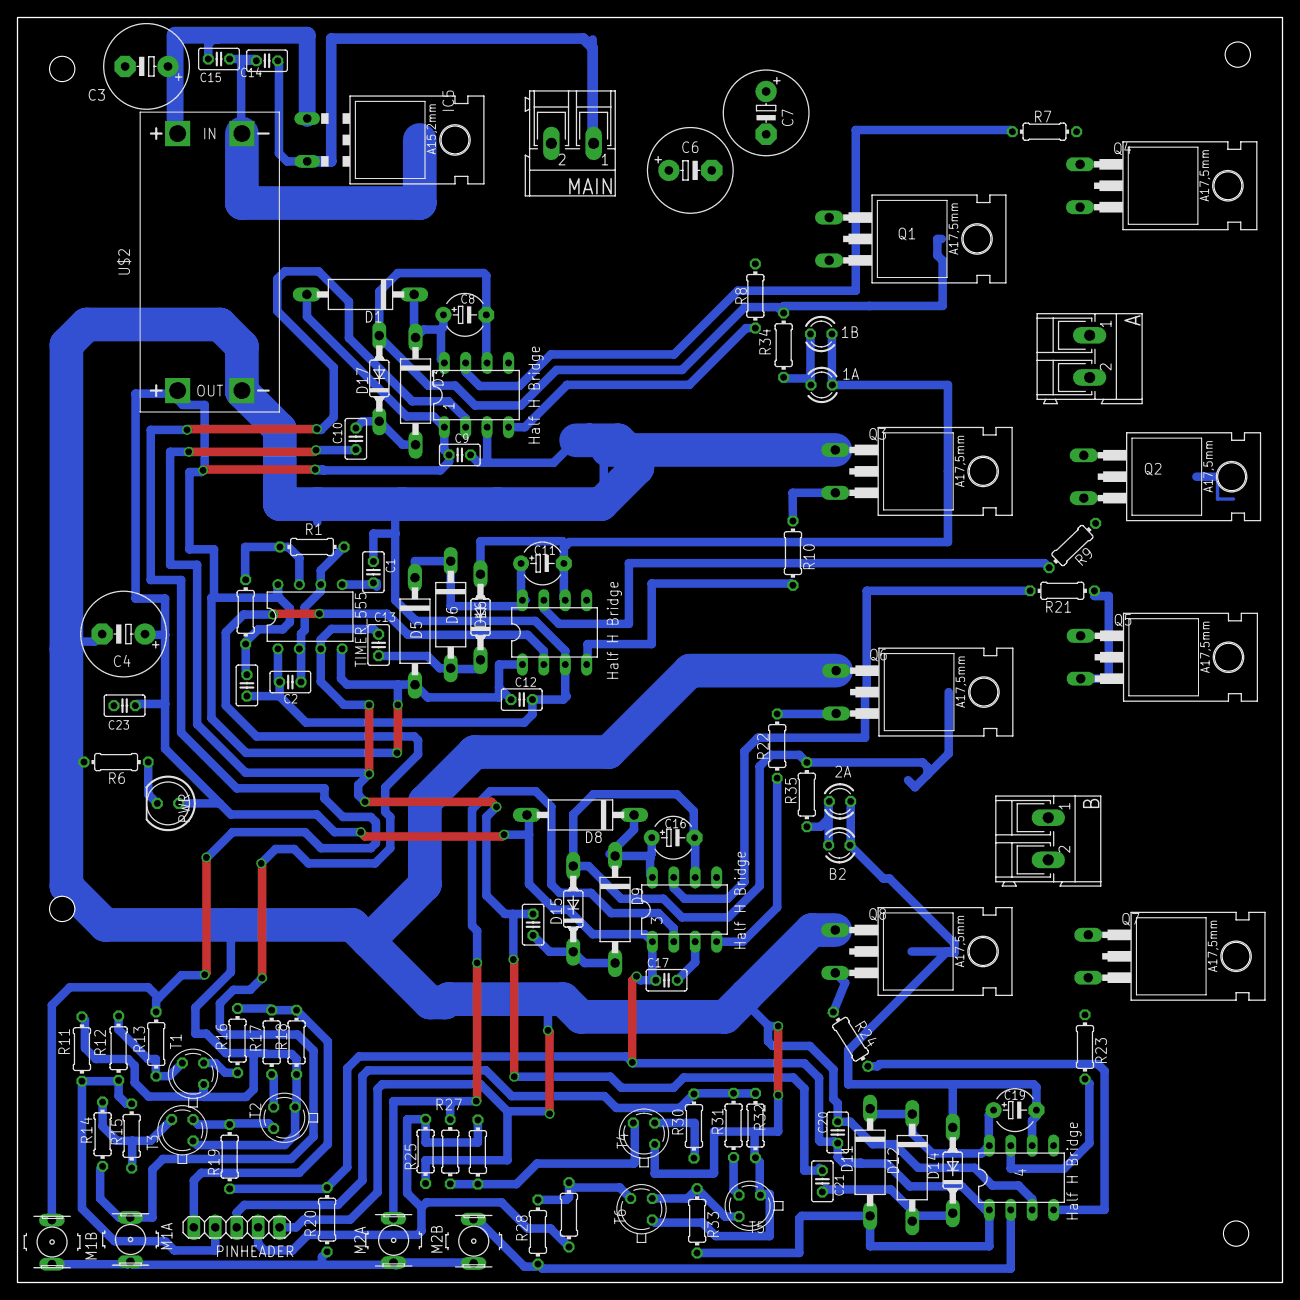
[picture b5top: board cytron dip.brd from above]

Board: 2 copper layers, 150.0 x 150.0 mm, 100 parts (0 on the bottom side), 58 nets.

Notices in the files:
parts and their libraries:
diy-modules: Released under the Creative Commons Attribution 4.0 International License: http://creativecommons.org/licenses/by/4.0
